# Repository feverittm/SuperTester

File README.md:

# SuperTester
First Robotics Electrical Tester
Unified Tester for most electronic controls on a FIRST Robotics robot.
Includes conntections for PWM, Spike, Analog, Digital (including encoder), and I2C (specific code for Accelerometer)
Needs to have CAN added.

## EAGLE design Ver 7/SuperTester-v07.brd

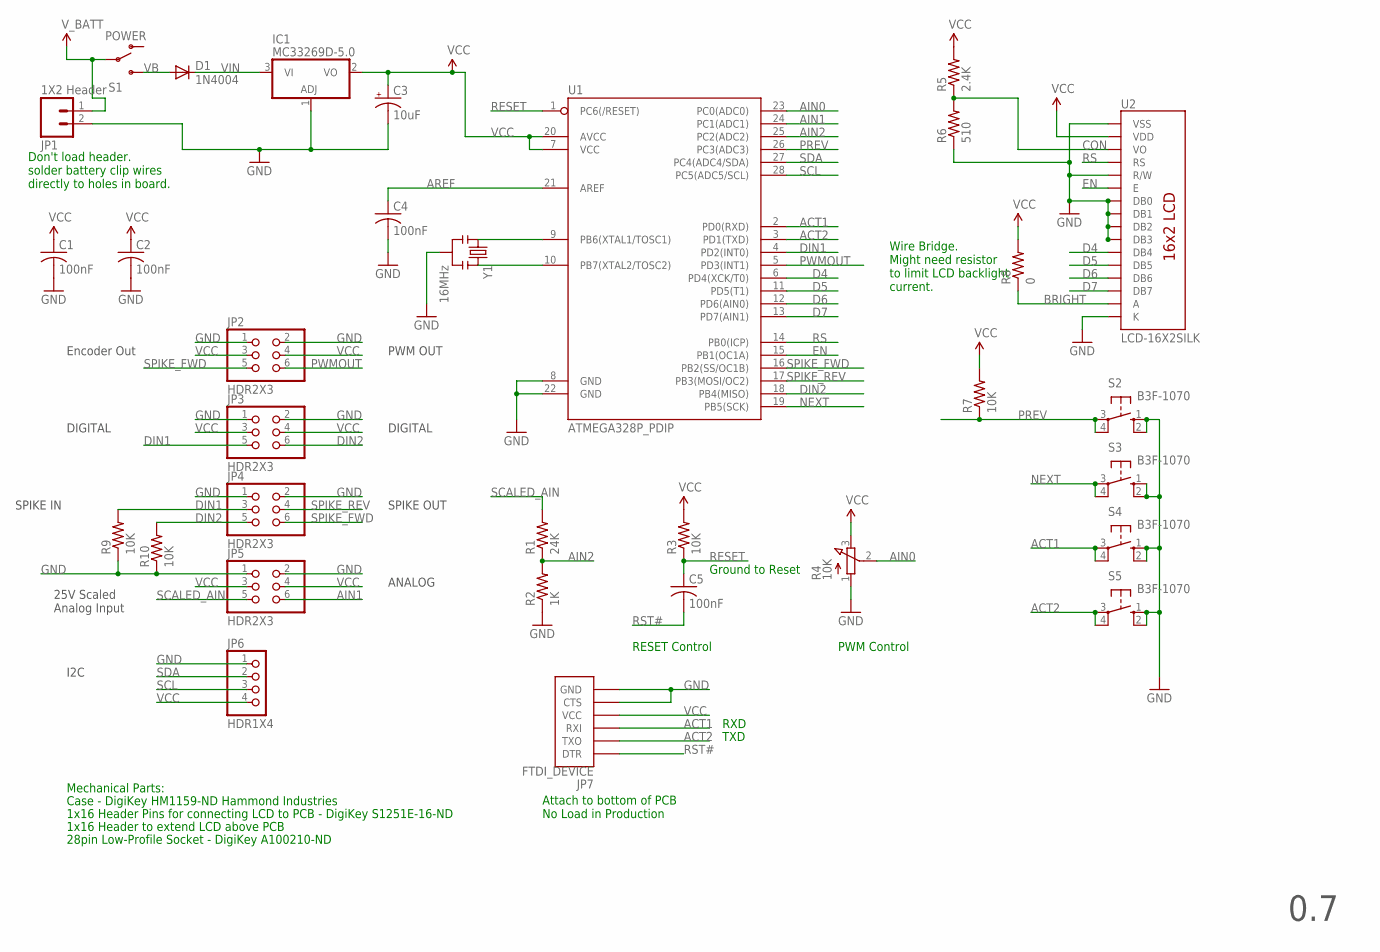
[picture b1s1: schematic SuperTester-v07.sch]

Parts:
C1, C2, C4, C5: 100nF; C025-025X050; PARTNO SR295E104MAR
C3: 10uF; E2,5-6E; PARTNO TAP106M025SCS
D1: 1N4004; DO41-10; PARTNO 1N4004GP-E3/54
IC1: MC33269D-5.0; DPACK; PARTNO MC33269DTRK-5.0G
JP1: 1X2 Header; 1X02; PARTNO 640456-2
JP2, JP3, JP4, JP5: HDR2X3; 2X03/90; PARTNO 68021-206HLF
JP6: HDR1X4; 1X04/90; PARTNO 68016-204HLF
JP7: FTDI_DEVICE; FTDI_DEVICE_SIDE; PARTNO 826926-6
R1: 24K; 0207/7; PARTNO CFR-12JB-52-24K
R2: 1K; 0207/7; PARTNO CFR-12JB-52-1K
R3, R7, R9, R10: 10K; 0207/7; PARTNO CFR-12JB-52-10K
R4: 10K; EVUF; PARTNO EVU-F3AF30B14
R5: 2.4K; 0207/7; PARTNO CFR-12JB-52-2K4
R6: 510; 0207/7; PARTNO CFR-12JB-52-510R
R8: 0; 0207/7; PARTNO ZOR-12-B-52-0R
S1: POWER; SWITCH-SPDT; PARTNO EG1218
S2, S3, S4, S5: B3F-1070; B3F-10XX; PARTNO B3F-1070
U1: ATMEGA328P_PDIP; DIL28-3; PARTNO ATMEGA328P-PU
U2: LCD-16X2SILK; LCD-16X2; PARTNO LCM-S01602DSF/A
Y1: 16MHz; RESONATOR-PTH; PARTNO CSTLS16M0X53-B0

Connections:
ACT1: JP7.P$3 (RXI), S4.3, S4.4 (P1), U1.2 (PD0(RXD))
ACT2: JP7.P$2 (TXO), S5.3, S5.4 (P1), U1.3 (PD1(TXD))
AIN0: R4.2 (S), U1.23 (PC0(ADC0))
AIN1: JP5.6, U1.24 (PC1(ADC1))
AIN2: R1.1, R2.2, U1.25 (PC2(ADC2))
AREF: C4.1, U1.21 (AREF)
BRIGHT: R8.1, U2.15 (A)
CON: R5.1, R6.2, U2.3 (VO)
D4: U1.6 (PD4(XCK/T0)), U2.11 (DB4)
D5: U1.11 (PD5(T1)), U2.12 (DB5)
D6: U1.12 (PD6(AIN0)), U2.13 (DB6)
D7: U1.13 (PD7(AIN1)), U2.14 (DB7)
DIN1: JP3.5, JP4.3, R9.2, U1.4 (PD2(INT0))
DIN2: JP3.6, JP4.5, R10.2, U1.18 (PB4(MISO))
EN: U1.15 (PB1(OC1A)), U2.6 (E)
GND: C1.2, C2.2, C3.-, C4.2, IC1.1 (ADJ), JP1.2, JP2.1, JP2.2, JP3.1, JP3.2, JP4.1, JP4.2, JP5.1, JP5.2, JP6.1, JP7.P$5 (CTS), JP7.P$6 (GND), R2.1, R4.1 (A), R6.1, R9.1, R10.1, S2.1 (S), S2.2 (S1), S3.1 (S), S3.2 (S1), S4.1 (S), S4.2 (S1), S5.1 (S), S5.2 (S1), U1.8 (GND), U1.22 (GND), U2.1 (VSS), U2.5 (R/W), U2.7 (DB0), U2.8 (DB1), U2.9 (DB2), U2.10 (DB3), U2.16 (K), Y1.2
NEXT: S3.3, S3.4 (P1), U1.19 (PB5(SCK))
PREV: R7.1, S2.3, S2.4 (P1), U1.26 (PC3(ADC3))
PWMOUT: JP2.6, U1.5 (PD3(INT1))
RESET: C5.1, R3.1, U1.1 (PC6(/RESET))
RS: U1.14 (PB0(ICP)), U2.4 (RS)
RST#: C5.2, JP7.P$1 (DTR)
SCALED_AIN: JP5.5, R1.2
SCL: JP6.3, U1.28 (PC5(ADC5/SCL))
SDA: JP6.2, U1.27 (PC4(ADC4/SDA))
SPIKE_FWD: JP2.5, JP4.6, U1.16 (PB2(SS/OC1B))
SPIKE_REV: JP4.4, U1.17 (PB3(MOSI/OC2))
VB: D1.A, S1.3 (S)
VCC: C1.1, C2.1, C3.+, IC1.2 (VO), JP2.3, JP2.4, JP3.3, JP3.4, JP5.3, JP5.4, JP6.4, JP7.P$4 (VCC), R3.2, R4.3 (E), R5.2, R7.2, R8.2, U1.7 (VCC), U1.20 (AVCC), U2.2 (VDD)
VIN: D1.C, IC1.3 (VI)
V_BATT: JP1.1, S1.2
XTAL1: U1.9 (PB6(XTAL1/TOSC1)), Y1.1
XTAL2: U1.10 (PB7(XTAL2/TOSC2)), Y1.3

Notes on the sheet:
PWM Control
Encoder Out
DIGITAL
ANALOG
PWM OUT
SPIKE OUT
I2C
25V Scaled Analog Input
RESET Control
Mechanical Parts:
Case - DigiKey HM1159-ND Hammond Industries
1x16 Header Pins for connecting LCD to PCB - DigiKey S1251E-16-ND
Attach to bottom of PCB No Load in Production
Wire Bridge. Might need resistor to limit LCD backlight current.
1x16 Header to extend LCD above PCB
0.7
SPIKE IN
28pin Low-Profile Socket - DigiKey A100210-ND
Don't load header. solder battery clip wires directly to holes in board.
RXD
TXD
Ground to Reset

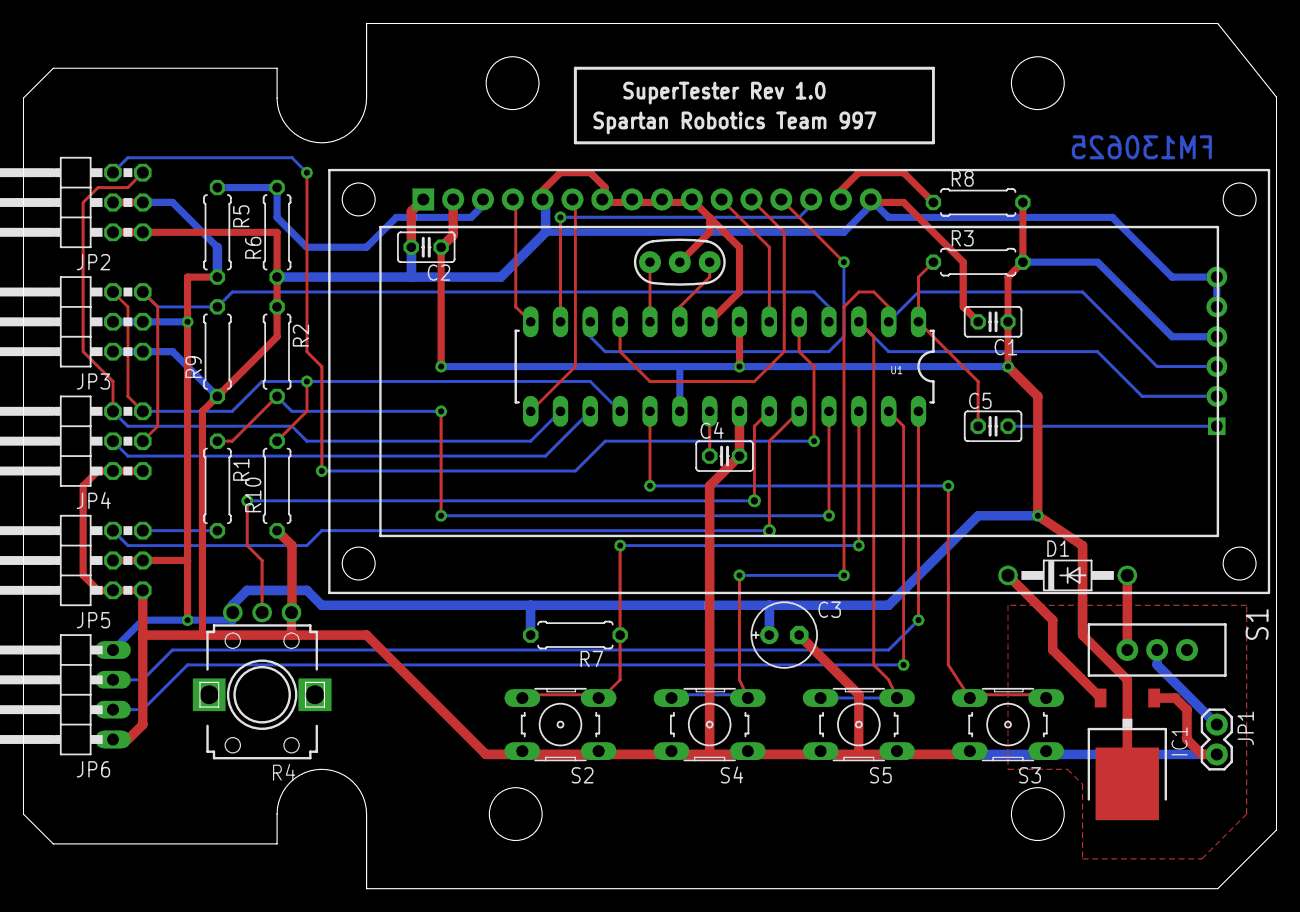
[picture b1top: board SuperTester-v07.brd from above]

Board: 2 copper layers, 106.7 x 73.7 mm, 32 parts (1 on the bottom side), 33 nets.

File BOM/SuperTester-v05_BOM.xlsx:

Board Level Parts
Qty | Part References | Value | Package | Mfg Part Num | Mfg Name | VID | Vendor Part Num | Description | XREF | Unit Price | Extended Price
1 | R8 | 0 | 0207/7 | ZOR-12-B-52-0R | Yageo | DK | 0.0EBK-ND | RES 0.0 OHM 1/6W JUMP AXIAL | REF35 | 0.1 | 0.1
1 | R2 | 1K | 0207/7 | CFR-12JB-52-1K | Yageo | DK | 1.0KEBK-ND | RES 1.0K OHM 1/6W 5% CARBON FILM | REF32 | 0.1 | 0.1
1 | D1 | 1N4004 | DO41-10 | 1N4004GP-E3/54 | Vishay Semiconductor | DK | 1N4004GP-E3/54GICT-ND | DIODE GEN PURP 400V 1A DO204AL | REF19 | 0.7 | 0.7
1 | JP1 | 1X2 Header | 1X02 | 640456-2 | TE Connectivity | DK | A1921-ND | CONN HEADER VERT 2POS .100 TIN | REF26 | 0.14000000000000001 | 0.14000000000000001
1 | R5 | 2.4K | 0207/7 | CFR-12JB-52-2K4 | Yageo | DK | 2.4KEBK-ND | RES 2.4K OHM 1/6W 5% CARBON FILM | REF34 | 0.1 | 0.1
4 | R3, R7, R9, R10 | 10K | 0207/7 | CFR-12JB-52-10K | Yageo | DK | 10KEBK-ND | RES 10K OHM 1/6W 5% CARBON FILM | REF31 | 7.6999999999999999E-2 | 0.308
1 | R4 | 10K | EVUF | EVU-F3AF30B14 | Panasonic Electronic Components | DK | P3A1103-ND | POT 10K OHM 9MM VERT NO BUSHING | REF38 | 1.05 | 1.05
1 | C3 | 10uF | E2,5-6E | TAP106M025SCS | AVX Corporation | DK | 478-5813-ND | CAP TANT 10UF 25V 20% RADIAL | REF39 | 0.86 | 0.86
1 | Y1 | 16MHz | RESONATOR-PTH | CSTLS16M0X53-B0 | Murata Electronics | DK | 490-7035-ND | CER RESONATOR | REF24 | 0.4 | 0.4
1 | R1 | 24K | 0207/7 | CFR-12JB-52-24K | Yageo | DK | 24KEBK-ND | RES 24K OHM 1/6W 5% CARBON FILM | REF33 | 0.1 | 0.1
4 | C1, C2, C4, C5 | 100nF | C025-025X050 | SR295E104MAR | AVX Corporation | DK | 478-5741-ND | CAP CER 0.1UF 50V 20% RADIAL | REF23 | 0.16700000000000001 | 0.66800000000000004
1 | R6 | 510 | 0207/7 | CFR-12JB-52-510R | Yageo | DK | 510EBK-ND | RES 510 OHM 1/6W 5% CARBON FILM | REF36 | 0.1 | 0.1
1 | U1 | ATMEGA328P_PDIP | DIL28-3 | ATMEGA328P-PU | Atmel | DK | ATMEGA328-PU-ND | IC MCU 8BIT 32KB FLASH 28DIP | REF21 | 2.88 | 2.88
4 | S2, S3, S4, S5 | B3F-1070 | B3F-10XX | B3F-1070 | Omron Electronics | DK | SW406-ND | SWITCH TACTILE SPST-NO 0.05A 24V | REF16 | 0.41699999999999998 | 1.6679999999999999
1 | JP7 | FTDI_DEVICE | FTDI_DEVICE_SIDE | 826926-6 | TE Connectivity | DK | A106757-ND | CONN HEADER BRKWAWAY 6POS TIN | REF27 | 0.45 | 0.45
1 | JP6 | HDR1X4 | 1X04/90 | 68016-204HLF | FCI | DK | 609-3319-ND | CONN HEADER 4POS .100 R/A 15AU | * | 0.19 | 0.19
4 | JP2, JP3, JP4, JP5 | HDR2X3 | 2X03/90 | 68021-206HLF | FCI | DK | 609-3343-ND | CONN HEADER 6POS .100 R/A 15AU | REF41 | 0.28999999999999998 | 1.1599999999999999
1 | U2 | LCD-16X2SILK | LCD-16X2 | LCM-S01602DSF/A | Lunex Opto/Components Inc | DK | 67-1758-ND | LCD MODULE 16X2 CHARACTER W/LED | REF37 | 13.45 | 0
1 | IC1 | MC33269D-5.0 | DPACK | MC33269DTRK-5.0G | ON Semiconductor | DK | MC33269DTRK-5.0GOSCT-ND | IC REG LDO 5V 0.8A DPAK | REF18 | 0.92 | 0.92
1 | S1 | POWER | SWITCH-SPDT | EG1218 | E-Switch | DK | EG1903-ND | SWITCH SLIDE SPDT 30V.2A PC MNT | REF40 | 0.55000000000000004 | 0.55000000000000004
 |  |  |  |  |  |  |  |  |  | Sub Total | 12.443999999999999
Case and Mechanical Parts
1 |  |  | Case | 153DTBUBKBAT | Hammond Manufacturing | DK | HM1159-ND | BOX ABS 5.8X3.5X0.98" TR BL | * | 10.15 | 10.15
1 |  |  | 1x16 Header | PBC16SFEN | Sullins Connector Solutions | DK | S1251E-16-ND | CONN HEADER .100 SINGL STR 16POS | * | 2.97 | 2.97
1 |  |  | 1x16 Socket | PPTC161LFBN-RC | Sullins Connector Solutions | DK | S7014-ND | CONN HEADER FEMALE 16POS 1" TIN | * | 1.22 | 1.22
1 |  |  | 28PIN IC Socket | 1-290261-9 | TE Connectivity | DK | A100210-ND | CONN IC SOCKET VERT 28POS TIN | * | 0.44 | 0.44
1 |  |  | Knob | 450-4760 | Eagle Plastic Devices | MO | 450-4760 | D-SHAFT PLASTIC KNOB | * | 0.66 | 0.66
 |  |  |  |  |  |  |  |  |  | Sub Total | 14.780000000000001
 |  |  |  |  |  |  |  |  |  | Total | 24.93

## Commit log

2015-01-16 removed orphin directory
2015-01-16 Added a code directory with the original V6 code from Tom Saksa
2016-07-25 Create README.md
    Supertester Description

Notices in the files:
parts and their libraries:
SparkFun-Displays: Licensing: CC v3.0 Share-Alike You are welcome to use this library for commercial purposes.
